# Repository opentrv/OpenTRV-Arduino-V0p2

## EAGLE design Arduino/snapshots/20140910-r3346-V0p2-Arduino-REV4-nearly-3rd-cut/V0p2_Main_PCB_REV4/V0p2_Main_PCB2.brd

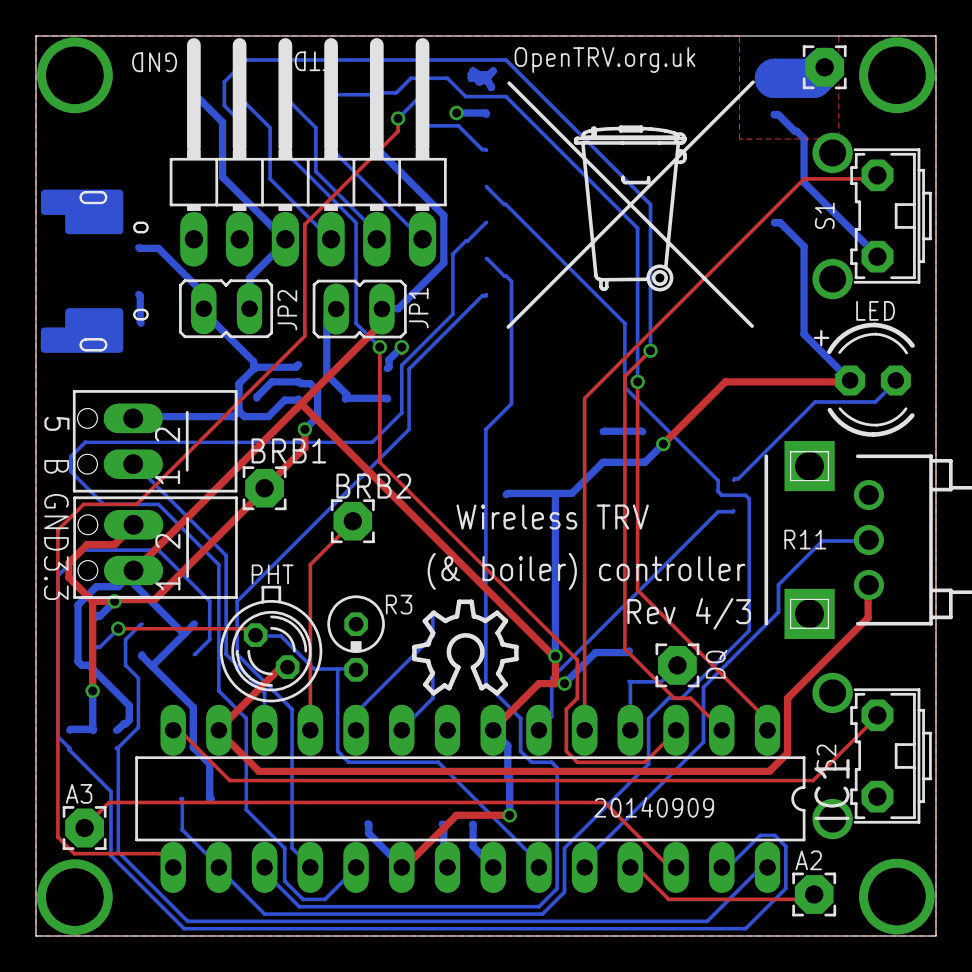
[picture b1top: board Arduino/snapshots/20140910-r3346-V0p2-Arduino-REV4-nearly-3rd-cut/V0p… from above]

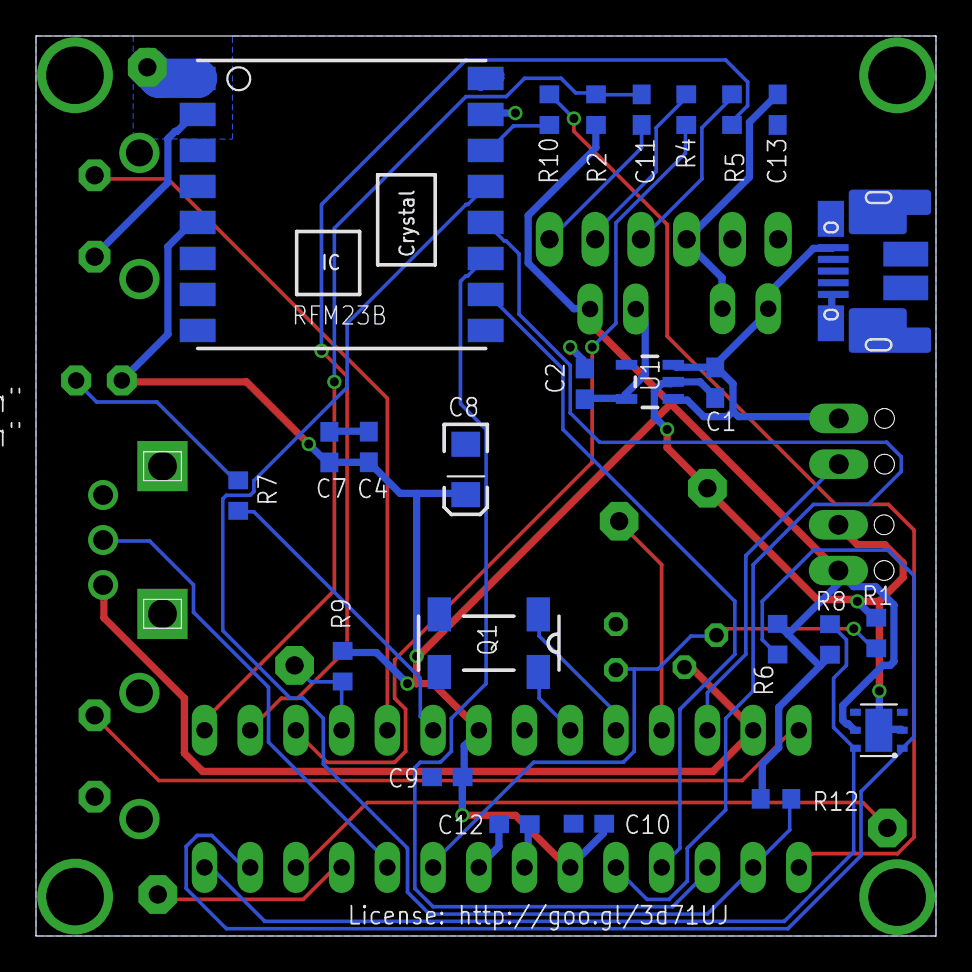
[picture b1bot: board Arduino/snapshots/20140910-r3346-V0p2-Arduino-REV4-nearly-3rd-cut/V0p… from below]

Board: 2 copper layers, 50.0 x 50.0 mm, 45 parts (25 on the bottom side), 35 nets.

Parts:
A2, A3: 2,15/1,0
ANT1: ANT (86 mm); 2,15/1,0
BRB1: BRB1; 2,15/1,0
BRB2: BRB2; 2,15/1,0
C1, C2, C13: 10uF 10V; C0603
C4: 100pF; C0603
C7, C9, C10, C11, C12: 100nF; C0603
C8: 100uF; EIA3216
DQ: 2,15/1,0
FTDI: 1X06/90
IC1: ATmega328P-PU; DIL28-3
JP1, JP2: JP1
LED: LED3MM
PHT: BPX65
Q1: 32768Hz; MC-306
R1: 220K; R0603
R2, R4, R5: 10K; R0603
R3: 0309V
R6, R8: 4K7; R0603
R7: 470R; R0603
R9: 4.7K; R0603
R10: 1K; R0603
R11: EVUE2A; EVUE
R12: 47K; R0603
RFM23B: RFM23B; RFM23-XXX-S1
S1, S2: B3F-31XX
U1: TC1185SMD; TC1185
U$1: OSHW_10X200_NOTEXT
U$2: TONNE
U$4: SHT21
USBPOWER: MICRO-USB-FCI-10103592
X1, X2: SCREWTERMINAL

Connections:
5V: C1.1, JP2.2, U1.1, U1.3, USBPOWER.1, X1.2
AI1: IC1.24, R11.2
BOILER: IC1.12, X1.1
BUTTON_LEARN2_L: IC1.5, S1.2
BUTTON_LEARN_L: IC1.14, S2.2
BUTTON_MODE_L: BRB2.1, IC1.11
D2: DQ.1, IC1.4, R9.1
GND: BRB1.1, C1.2, C2.1, C4.1, C7.2, C8.C, C9.2, C10.2, C12.2, C13.1, FTDI.1, FTDI.2, IC1.8, IC1.22, R1.2, R3.1, R11.3, RFM23B.2, RFM23B.9, RFM23B.15, RFM23B.16, S1.1, S2.1, U1.2, U$4.2, U$4.P$1, USBPOWER.5, USBPOWER.7, USBPOWER.17, X2.2
IO_POWER_UP: IC1.13, PHT.K, R11.1
LDR: IC1.23, PHT.A, R1.1, R3.2
LED_HEATCALL_L: IC1.6, R7.1
unnamed: C11.2, FTDI.6
unnamed: FTDI.4, R5.2
unnamed: FTDI.5, R4.2
unnamed: C12.1, IC1.21
unnamed: R10.2, RFM23B.14
unnamed: C2.2, JP1.1, U1.5
unnamed: C13.2, FTDI.3, JP2.1
unnamed: LED.K, R7.2
unnamed: A2.1, IC1.25
unnamed: A3.1, IC1.26
unnamed: ANT1.1, RFM23B.1
RESET: C11.1, IC1.1, R2.2
RFM_IRQ: IC1.15, R10.1
RX: IC1.3, R4.1
SCL: IC1.28, R8.1, U$4.6
SDA: IC1.27, R6.2, U$4.1
SPI_MISO: IC1.18, RFM23B.10
SPI_MOSI: IC1.17, RFM23B.11
SPI_NSS: IC1.16, R12.1, RFM23B.13
SPI_SCK: IC1.19, RFM23B.12
TX: IC1.2, R5.1
VCC: C4.2, C7.1, C8.A, C9.1, C10.1, IC1.7, IC1.20, JP1.2, LED.A, R2.1, R6.1, R8.2, R9.2, R12.2, RFM23B.5, U$4.5, X2.1
XTAL1: IC1.9, Q1.4
XTAL2: IC1.10, Q1.1

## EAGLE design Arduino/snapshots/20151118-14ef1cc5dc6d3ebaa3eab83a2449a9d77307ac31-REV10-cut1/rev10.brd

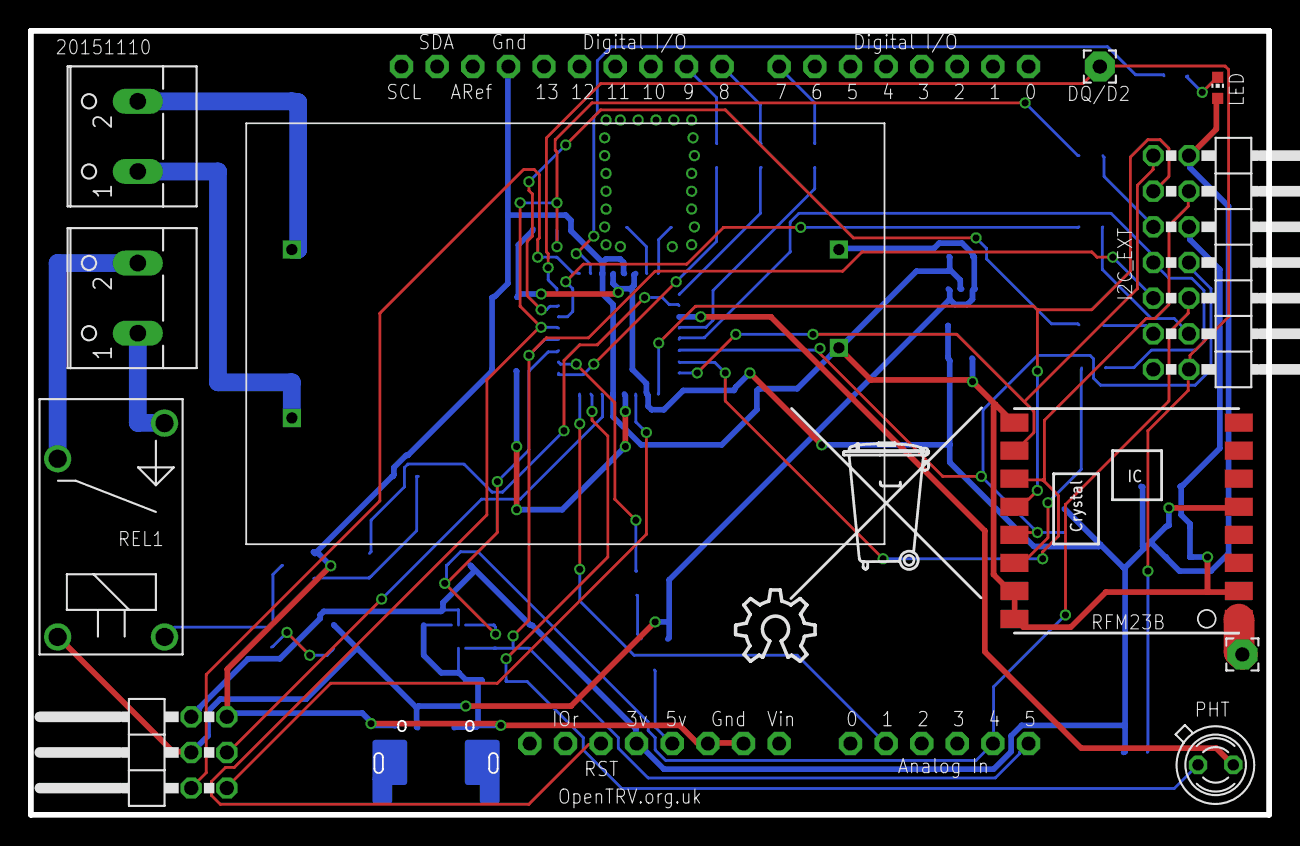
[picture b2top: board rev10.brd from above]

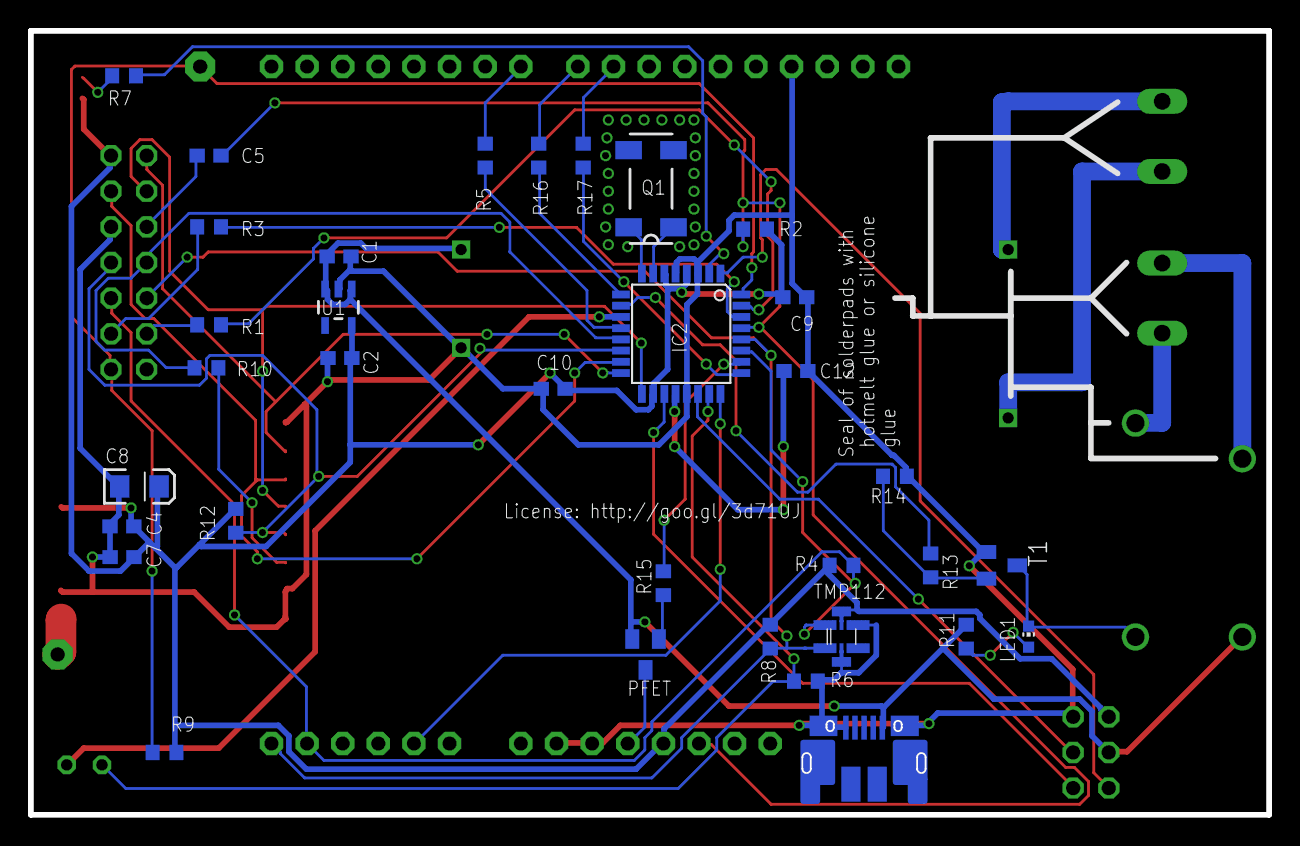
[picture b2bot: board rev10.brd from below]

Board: 2 copper layers, 88.3 x 55.9 mm, 48 parts (34 on the bottom side), 47 nets.

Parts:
ANT1: ANT (86 mm); 2,15/1,0
C1, C2: 10uF 10V; C0603
C4: 100pF; C0603
C5, C7, C9, C10, C12: 100nF; C0603
C8: 100uF; EIA3216
DQ/D2: 2,15/1,0
I2C_EXT: 2X07/90
IC2: ATMEGA168-AU; TQFP32-08
JP2: 2X03/90
LED, LED1: CHIP-LED0603
PFET: BSS84; SOT23
PHT: BPX65
PSU: VTX-214-010-205
Q1: 32768Hz; MC-306
R1, R2, R3, R5, R9, R12, R15, R17: 4.7K; R0603
R4, R8: 4K7; R0603
R6: 100K; R0603
R7, R11: 470R; R0603
R10, R13: 1K; R0603
R14: 10K; R0603
R16: 330R; R0603
REL1: OJE-SS-103HM
RFM23B: RFM23B; RFM23-XXX-S1
T1: SOT23-EBC
TMP112: TMP1; TMP112
U1: TC1185SMD; TC1185
U2: ARDUINO
U$1: OSHW_10X200_NOTEXT
U$2: TONNE
USBPOWER: MICRO-USB-FCI-10103592
X1, X3: W237-102

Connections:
5V: C1.1, JP2.4, PFET.2, PSU.+, R11.2, REL1.S2, U1.1, U1.3, USBPOWER.1
5VGSM: PFET.3, U2.5V
BOILER: IC2.10, R13.1
D2: DQ/D2.1, I2C_EXT.14, IC2.32, R9.1
GND: C1.2, C2.1, C4.1, C7.2, C8.C, C9.2, C10.2, C12.2, I2C_EXT.6, IC2.3, IC2.5, IC2.21, JP2.5, PSU.-, R6.2, R14.1, RFM23B.2, RFM23B.9, RFM23B.15, RFM23B.16, T1.E, TMP112.2, TMP112.4, U1.2, U2.GND, U2.GND1, U2.GND2, USBPOWER.5, USBPOWER.7, USBPOWER.17
IO_POWER_UP: IC2.11, PHT.K
LDR: IC2.23, PHT.A, R6.1
LED_HEATCALL_L: IC2.2, R7.1
unnamed: IC2.19, JP2.1
unnamed: IC2.12, R5.1
unnamed: PSU.N, X1.2
unnamed: IC2.22, JP2.3
unnamed: C12.1, IC2.20
unnamed: R10.2, RFM23B.14
unnamed: PSU.L, X1.1
unnamed: IC2.25, R17.2
unnamed: R13.2, R14.2, T1.B
unnamed: LED.C, R7.2
unnamed: LED1.C, REL1.S1, T1.C
unnamed: IC2.24, U2.A1
unnamed: LED1.A, R11.1
unnamed: PFET.1, R15.1
unnamed: R5.2, U2.D7
unnamed: IC2.9, R16.2
unnamed: REL1.C, X3.2
unnamed: REL1.S, X3.1
unnamed: C5.2, I2C_EXT.5
unnamed: I2C_EXT.12, R3.2
unnamed: I2C_EXT.11, R1.2
unnamed: R17.1, U2.D9
unnamed: ANT1.1, RFM23B.1
unnamed: R16.1, U2.D8
PFET: IC2.26, R15.2
RESET: C5.1, IC2.29, R2.2, U2.RESET
RFM_IRQ: I2C_EXT.7, IC2.13, R10.1
RX: IC2.31, R1.1
SCL: I2C_EXT.9, IC2.28, R8.1, TMP112.1, U2.A5
SDA: I2C_EXT.10, IC2.27, R4.2, TMP112.6, U2.A4
SPI_MISO: I2C_EXT.1, IC2.16, RFM23B.10
SPI_MOSI: I2C_EXT.4, IC2.15, RFM23B.11
SPI_NSS: I2C_EXT.8, IC2.14, R12.1, RFM23B.13
SPI_SCK: I2C_EXT.3, IC2.17, RFM23B.12
TX: IC2.30, R3.1
VCC: C2.2, C4.2, C7.1, C8.A, C9.1, C10.1, I2C_EXT.2, IC2.4, IC2.6, IC2.18, JP2.6, LED.A, R2.1, R4.1, R8.2, R9.2, R12.2, RFM23B.5, TMP112.5, U1.5, U2.3V
VOICE: IC2.1, JP2.2
XTAL1: IC2.7, Q1.1
XTAL2: IC2.8, Q1.4

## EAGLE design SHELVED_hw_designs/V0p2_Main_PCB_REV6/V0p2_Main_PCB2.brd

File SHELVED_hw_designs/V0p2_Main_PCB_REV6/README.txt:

REV 6 is SMD AVR, RFM23B, and phototransistor and TMP122 and SHT21 temp+RH sensor
and I2C extension connector.

Using ATmega pinout for Eagle from:
http://www.faludi.com/2008/10/07/arduino-avr-library-for-eagle-layout-editor/
without explicit licence but following email permission:

    From: Rob Faludi
    Date: 13 May 2013 00:34:52 GMT+01:00
    Subject: Re: A comment from Damon Hart-Davis

    Sure, go for it!

    A new submission (form: "Contact Form")
    ============================================
    Submitted on: May 12, 2013
    Via: /contact/

    --------------------------Contact Me----------------------

    Your Name:                      Damon Hart-Davis

    Message:
    May we use your Eagle ATmega package/library:

    http://www.faludi.com/2008/10/07/arduino-avr-library-for-eagle-layout-editor/

    In our Apache/Solderpad-licenced OpenTRV project please?

    Rgds

    Damon
    http://opentrv.org.uk/

Note ITEADstudio .dru and .cam files downloaded from their site AND NOT COVERED BY OUR APACHE LICENCE
though ITEADstudio would probably be happy for you to use their service like we did!

Component-ordering document: ??

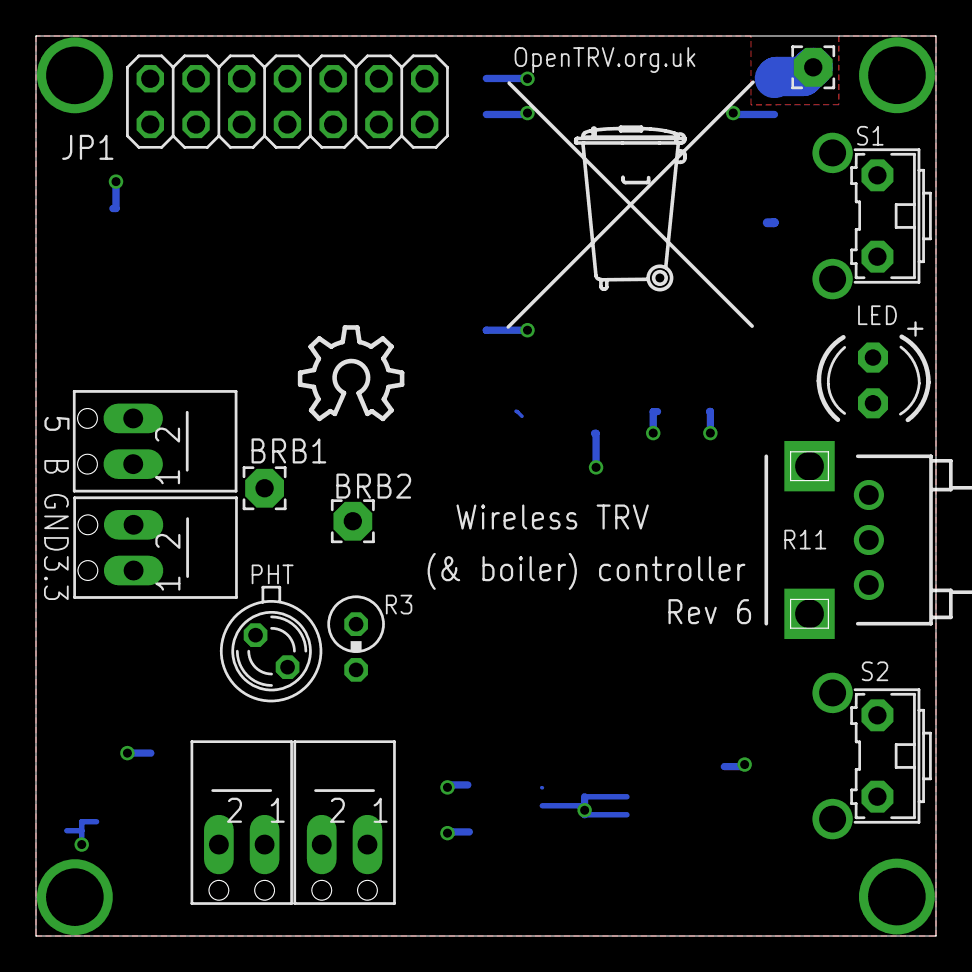
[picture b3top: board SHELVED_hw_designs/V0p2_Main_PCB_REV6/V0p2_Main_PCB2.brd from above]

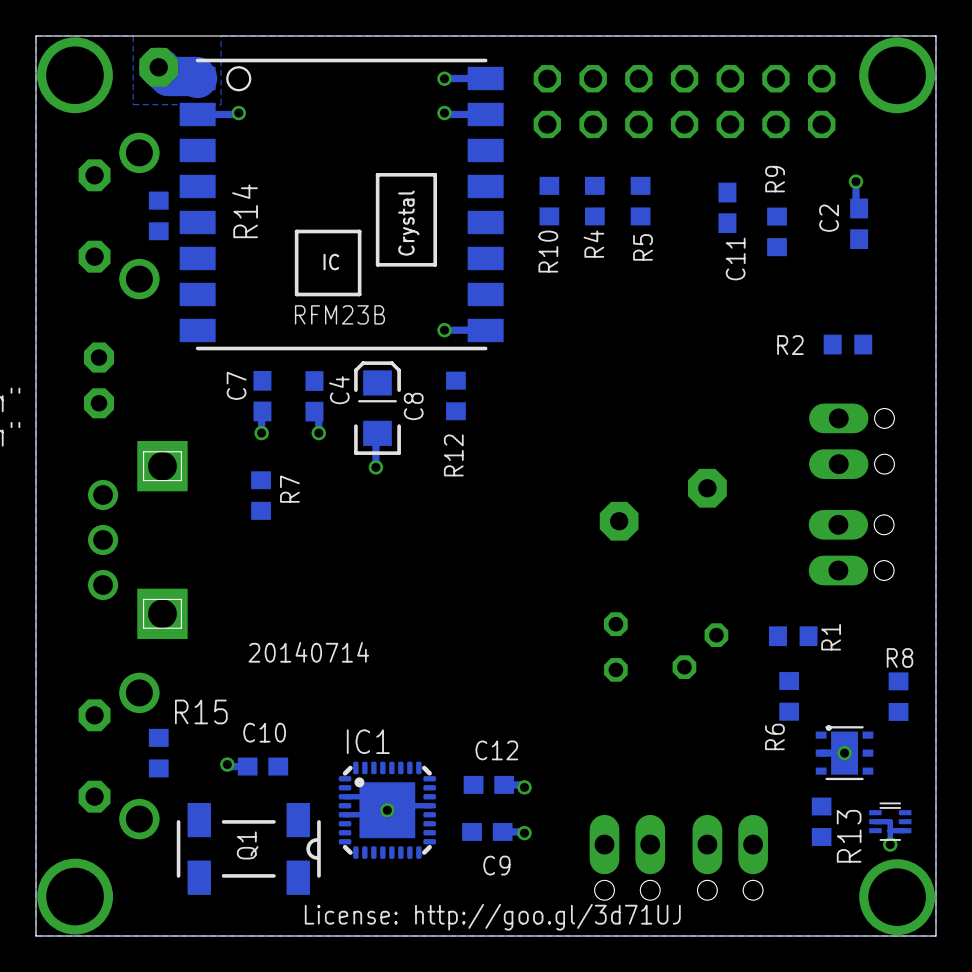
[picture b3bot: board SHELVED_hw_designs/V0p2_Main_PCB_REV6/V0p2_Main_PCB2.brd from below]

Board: 2 copper layers, 50.0 x 50.0 mm, 42 parts (26 on the bottom side), 35 nets.

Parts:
ANT1: ANT (86 mm); 2,15/1,0
BRB1: BRB1; 2,15/1,0
BRB2: BRB2; 2,15/1,0
C2: 10uF 10V; C0603
C4: 100pF; C0603
C7, C9, C10, C11, C12: 100nF; C0603
C8: 100uF; EIA3216
IC1: ATMEGA???-MU; MLF32
JP1: 2X07
LED: LED3MM
PHT: BPX65
Q1: 32768Hz; MC-306
R1: 220K; R0603
R2: 10K; R0603
R3: 0309V
R4, R5, R9, R10: 4.7K; R0603
R6, R8, R14, R15: 4K7; R0603
R7: 470R; R0603
R11: EVUE2A; EVUE
R12: 47K; R0603
R13: 1R; R0603
RFM23B: RFM23B; RFM23-XXX-S1
S1, S2: B3F-31XX
TMP1: TMP1; TMP112
U$1: OSHW_10X200_NOTEXT
U$2: TONNE
U$4: SHT21
X1, X2, X3, X4: SCREWTERMINAL

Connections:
BOILER: IC1.10, X1.1
BUTTON_LEARN2_L: IC1.1, R14.1, S1.2
BUTTON_LEARN_L: IC1.12, R15.1, S2.2
BUTTON_MODE_L: BRB2.1, IC1.9
DQ: IC1.32, JP1.14, R9.1
GND: BRB1.1, C2.1, C4.1, C7.2, C8.C, C9.2, C10.2, C12.2, IC1.3, IC1.5, IC1.21, IC1.P$1, JP1.6, R1.2, R3.1, R11.3, RFM23B.2, RFM23B.9, RFM23B.15, RFM23B.16, S1.1, S2.1, TMP1.2, TMP1.4, U$4.2, U$4.P$1, X2.2
IO_POWER_UP: IC1.11, PHT.K, R11.1
LDR: IC1.23, PHT.A, R1.1, R3.2
LED_HEATCALL_L: IC1.2, R7.1
MC: IC1.22, X4.1
MI: IC1.19, X4.2
ML: IC1.25, X3.2
MR: IC1.26, X3.1
unnamed: C11.2, JP1.5
unnamed: JP1.12, R5.2
unnamed: JP1.11, R4.2
unnamed: C12.1, IC1.20
unnamed: R10.2, RFM23B.14
unnamed: C10.1, IC1.18, R13.1
unnamed: LED.K, R7.2
unnamed: ANT1.1, RFM23B.1
POT: IC1.24, R11.2
RESET: C11.1, IC1.29, R2.2
RFM_IRQ: IC1.13, JP1.7, R10.1
RXD0: IC1.31, R4.1
SCL: IC1.28, JP1.9, R8.1, U$4.6
SDA: IC1.27, JP1.10, R6.2, U$4.1
SPI_MISO: IC1.16, JP1.1, RFM23B.10
SPI_MOSI: IC1.15, JP1.4, RFM23B.11
SPI_NSS: IC1.14, JP1.8, R12.1, RFM23B.13
SPI_SCK: IC1.17, JP1.3, RFM23B.12
TXD0: IC1.30, R5.1
VCC: C2.2, C4.2, C7.1, C8.A, C9.1, IC1.4, IC1.6, JP1.2, LED.A, R2.1, R6.1, R8.2, R9.2, R12.2, R13.2, R14.2, R15.2, RFM23B.5, TMP1.5, U$4.5, X2.1
XTAL1: IC1.7, Q1.1
XTAL2: IC1.8, Q1.4

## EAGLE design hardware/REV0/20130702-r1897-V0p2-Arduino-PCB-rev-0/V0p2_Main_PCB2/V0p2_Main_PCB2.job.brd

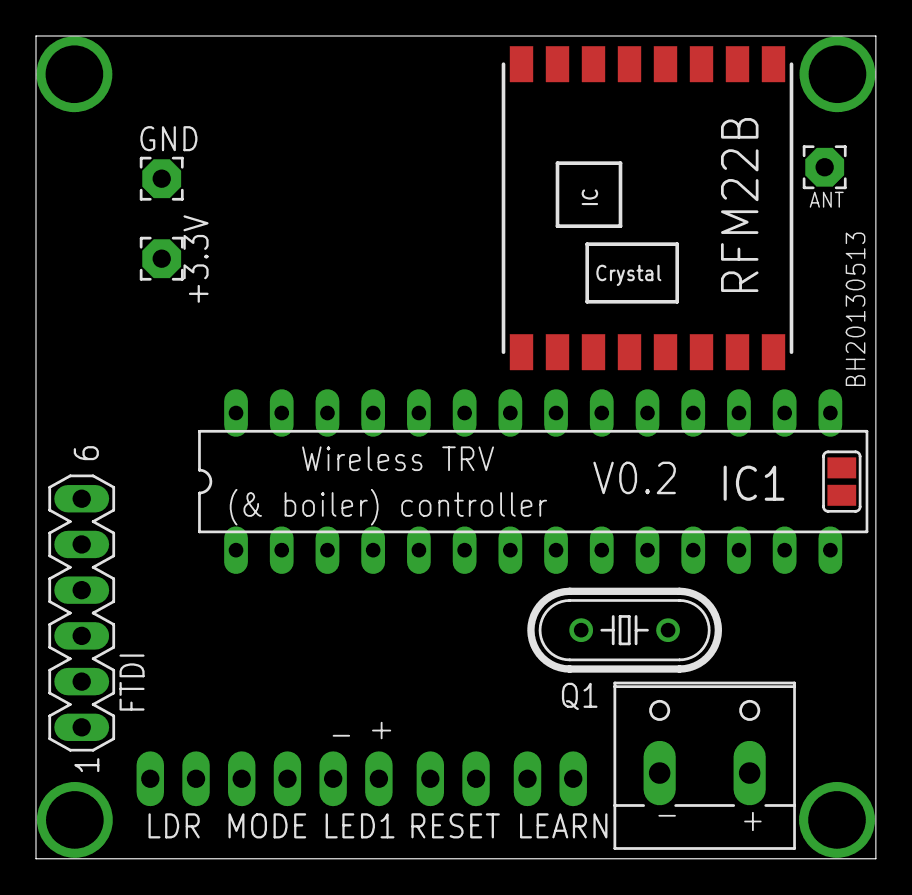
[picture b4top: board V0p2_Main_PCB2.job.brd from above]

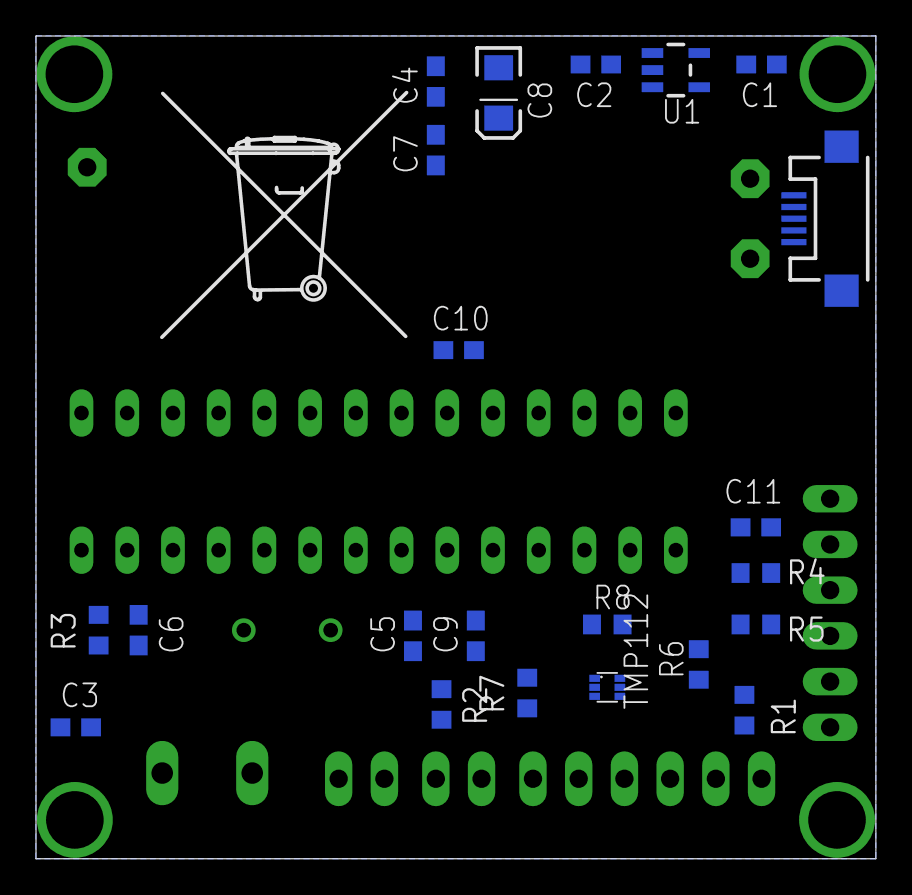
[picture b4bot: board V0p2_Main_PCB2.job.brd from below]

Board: 2 copper layers, 46.7 x 45.7 mm, 38 parts (23 on the bottom side), 27 nets, no tracks yet.

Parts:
5V: USB-MICROB
+3.3V: 2,15/1,0
-: BOILER; W237-102
ANT: ANT (86 mm); 2,15/1,0
C1, C2: 10uF 10V; 0603-CAP
C3, C7, C9, C10, C11: 100nF; 0603-CAP
C4: 100pF; 0603-CAP
C5, C6: 0pF; 0603-CAP
C8: 100uF; EIA3216
FTDI: FTDI; MA06-1
GND: 2,15/1,0
IC1: ATMEGA328P-PU; DIL28-3
LDR: 1X02
LEARN: 1X02
LED1: 1X02
MODE: 1X02
Q1: 32768Hz; HC49/S
R1: 100K; R0603
R2, R4, R5: 10K; R0603
R3: 330R; R0603
R6, R8: 4K7; R0603
R7: 470R; R0603
RESET: 1X02
RFM22B: RFM22SMD; RFM22-XXX-S2
SJ1: SJ
TMP112: TMP112
U1: TC1185SMD; TC1185
U$2: TONNE
U$3: OSHW_6X200_NOTEXT

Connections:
5V: 5V.VBUS, C1.1, FTDI.3, U1.1, U1.3
BOILER: -.2, IC1.12
BUTTON_LEARN_L: IC1.14, LEARN.1
BUTTON_MODE_L: IC1.11, MODE.1
GND: 5V.GND, 5V.MT1, 5V.MT2, -.1, C1.2, C2.1, C4.2, C5.2, C6.2, C7.1, C8.C, C9.2, C10.2, FTDI.1, FTDI.2, GND.1, IC1.8, IC1.22, LEARN.2, LED1.1, MODE.2, R1.2, RESET.1, RFM22B.2, RFM22B.9, RFM22B.15, RFM22B.16, TMP112.2, TMP112.4, U1.2
IO_POWER: C3.1, LDR.2
IO_POWER_UP: IC1.13, R3.1
LDR: IC1.23, LDR.1, R1.1
LEDEXT: LED1.2, R7.2
LED_HEATCALL: R7.1, SJ1.2
unnamed: C11.2, FTDI.6
unnamed: C3.2, R3.2
unnamed: RFM22B.3, RFM22B.6
unnamed: RFM22B.4, RFM22B.7
unnamed: ANT.1, RFM22B.1
RESET: C11.1, IC1.1, R2.2, RESET.2
RX: FTDI.5, R4.1, R4.2
SCL: IC1.28, R8.1, TMP112.1
SDA: IC1.27, R6.2, TMP112.6
SPI_MISO: IC1.18, RFM22B.10
SPI_MOSI: IC1.17, RFM22B.11
SPI_NSS: IC1.16, RFM22B.13
SPI_SCK: IC1.19, RFM22B.12, SJ1.1
TX: FTDI.4, R5.1, R5.2
VCC: +3.3V.1, C2.2, C4.1, C7.2, C8.A, C9.1, C10.1, IC1.7, IC1.20, R2.1, R6.1, R8.2, RFM22B.5, TMP112.5, U1.5
XTAL1: C5.1, IC1.9, Q1.2
XTAL2: C6.1, IC1.10, Q1.1

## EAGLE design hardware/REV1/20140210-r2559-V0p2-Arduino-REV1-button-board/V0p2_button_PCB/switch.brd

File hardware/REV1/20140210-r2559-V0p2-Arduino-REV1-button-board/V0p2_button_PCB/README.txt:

PCB to carry front-panel-mounted UI components, etc.  LED, buttons, LDR, for REV1 of main PCB onwards.

REV1:
https://docs.google.com/spreadsheet/ccc?key=0AkWwv0Q6wTaZdGZCcmlXR25tT0YwWmFfb1RUaDgtZUE&usp=drive_web#gid=0

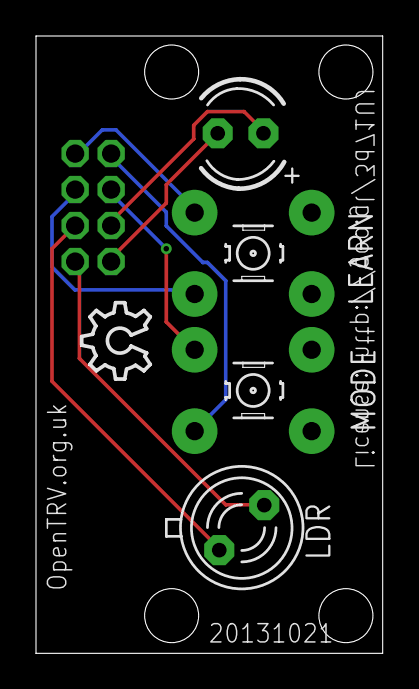
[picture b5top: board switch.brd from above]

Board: 2 copper layers, 19.3 x 34.3 mm, 6 parts (1 on the bottom side), 8 nets.

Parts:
JP10: 2X04
LDR: BPX65
LEARN: B3F-10XX
LED1: LED3MM
MODE: B3F-10XX
U$1: OSHW_8X150_NOTEXT

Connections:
unnamed: JP10.1, MODE.2
unnamed: JP10.4, LEARN.2
unnamed: JP10.2, LEARN.4
unnamed: JP10.3, MODE.4
unnamed: JP10.7, LED1.K
unnamed: JP10.5, LED1.A
unnamed: JP10.6, LDR.A
unnamed: JP10.8, LDR.K

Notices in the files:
Arduino/snapshots/20140910-r3346-V0p2-Arduino-REV4-nearly-3rd-cut/V0p2_Main_PCB_REV4/V0p2_Main_PCB2.brd:
License: http://goo.gl/3d71UJ
parts and their libraries:
SparkFun-Passives: Licensing: CC v3.0 Share-Alike You are welcome to use this library for commercial purposes.
